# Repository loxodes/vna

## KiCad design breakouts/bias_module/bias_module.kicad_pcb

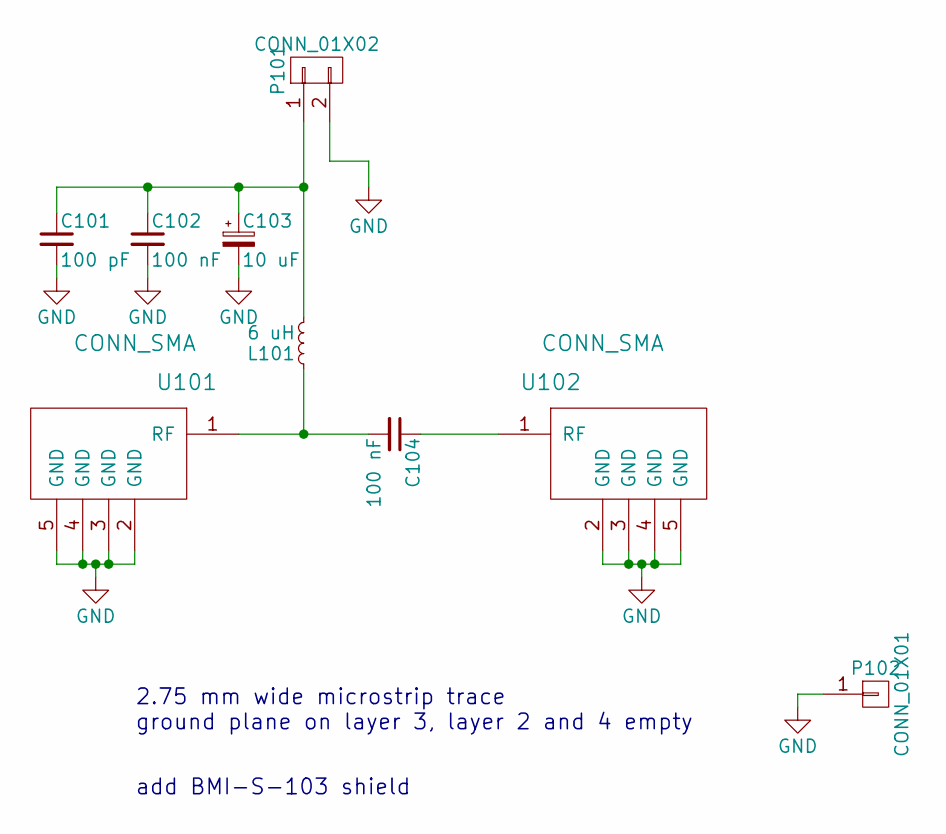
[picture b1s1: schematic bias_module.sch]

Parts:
C101: 100 pF; C_0402
C102: 100 nF; C_0603
C103: 10 uF; C_0805
C104: 100 nF; ATC550L
L101: 6 uH; ATC506WLS
P101: CONN_01X02; TerminalBlock_Pheonix_PT-3.5mm_2pol
P102: CONN_01X01; BMI-S-103-NOSIDES
U101, U102: CONN_SMA; 732511150_sma_thin

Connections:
GND: C101.2, C102.2, C103.2, P101.2, P102.1, U101.2 (GND), U101.3 (GND), U101.4 (GND), U101.5 (GND), U102.2 (GND), U102.3 (GND), U102.4 (GND), U102.5 (GND)
unnamed: C101.1, C102.1, C103.1, L101.2, P101.1
unnamed: C104.1, U102.1 (RF)
unnamed: C104.2, L101.1, U101.1 (RF)

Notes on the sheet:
2.75 mm wide microstrip trace ground plane on layer 3, layer 2 and 4 empty
add BMI-S-103 shield

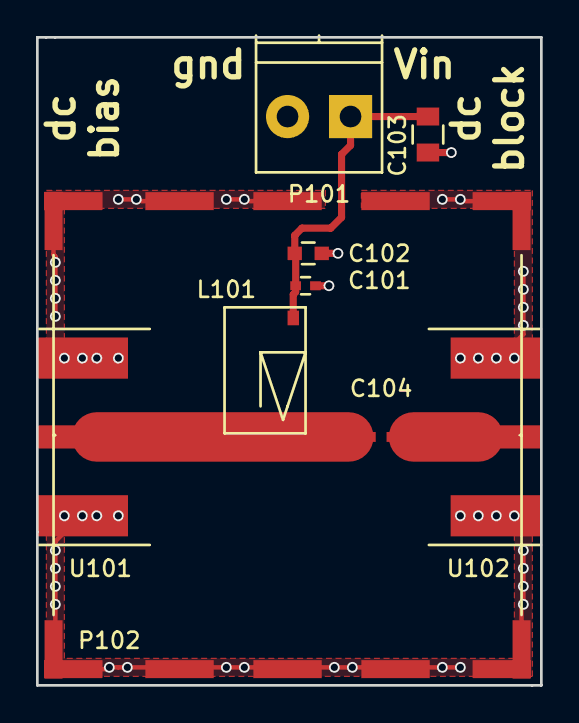
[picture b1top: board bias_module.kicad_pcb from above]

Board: 4 copper layers, 28.0 x 36.0 mm, 9 parts (0 on the bottom side), 4 nets.

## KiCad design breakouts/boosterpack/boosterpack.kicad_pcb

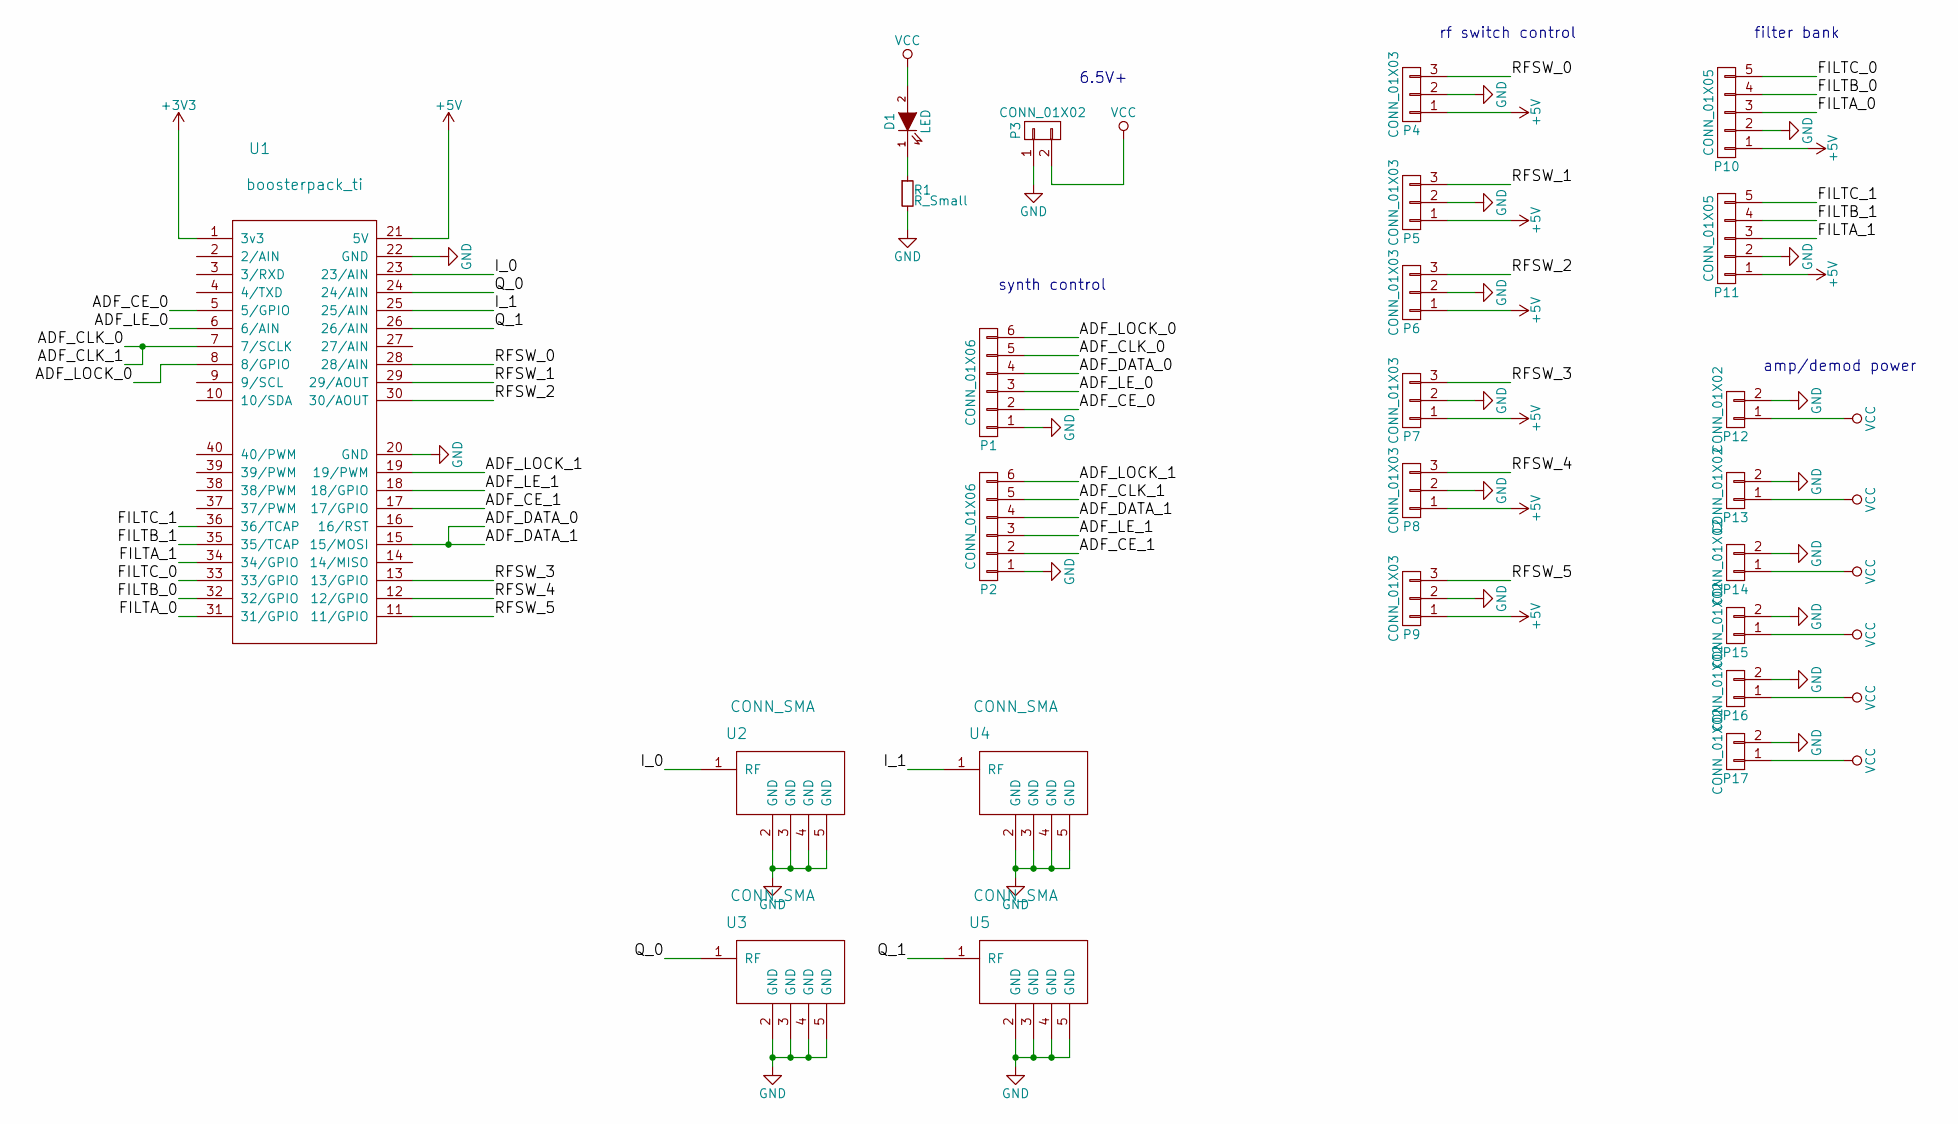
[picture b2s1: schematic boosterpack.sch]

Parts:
D1: LED; LED_0603
P1, P2: CONN_01X06; Pin_Header_Straight_1x06
P3: CONN_01X02; TerminalBlock_Pheonix_PT-3.5mm_2pol
P4, P5, P6, P7, P8, P9: CONN_01X03; Pin_Header_Straight_1x03
P10, P11: CONN_01X05; Pin_Header_Straight_1x05
P12, P13, P14, P15, P16, P17: CONN_01X02; Pin_Header_Straight_1x02
R1: R_Small; R_0603
U1: boosterpack_ti; ti_booster40
U2, U3, U4, U5: CONN_SMA; 732512200_SMA

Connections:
+3V3: U1.1 (3v3)
+5V: P4.1, P5.1, P6.1, P7.1, P8.1, P9.1, P10.1, P11.1, U1.21 (5V)
/ADF_CE_0: P1.2, U1.5 (5/GPIO)
/ADF_CE_1: P2.2, U1.17 (17/GPIO)
/ADF_CLK_0: P1.5, P2.5, U1.7 (7/SCLK)
/ADF_DATA_0: P1.4, P2.4, U1.15 (15/MOSI)
/ADF_LE_0: P1.3, U1.6 (6/AIN)
/ADF_LE_1: P2.3, U1.18 (18/GPIO)
/ADF_LOCK_0: P1.6, U1.8 (8/GPIO)
/ADF_LOCK_1: P2.6, U1.19 (19/PWM)
/FILTA_0: P10.3, U1.31 (31/GPIO)
/FILTA_1: P11.3, U1.34 (34/GPIO)
/FILTB_0: P10.4, U1.32 (32/GPIO)
/FILTB_1: P11.4, U1.35 (35/TCAP)
/FILTC_0: P10.5, U1.33 (33/GPIO)
/FILTC_1: P11.5, U1.36 (36/TCAP)
/I_0: U1.23 (23/AIN), U2.1 (RF)
/I_1: U1.25 (25/AIN), U4.1 (RF)
/Q_0: U1.24 (24/AIN), U3.1 (RF)
/Q_1: U1.26 (26/AIN), U5.1 (RF)
/RFSW_0: P4.3, U1.28 (28/AIN)
/RFSW_1: P5.3, U1.29 (29/AOUT)
/RFSW_2: P6.3, U1.30 (30/AOUT)
/RFSW_3: P7.3, U1.13 (13/GPIO)
/RFSW_4: P8.3, U1.12 (12/GPIO)
/RFSW_5: P9.3, U1.11 (11/GPIO)
GND: P1.1, P2.1, P3.1, P4.2, P5.2, P6.2, P7.2, P8.2, P9.2, P10.2, P11.2, P12.2, P13.2, P14.2, P15.2, P16.2, P17.2, R1.2, U1.20 (GND), U1.22 (GND), U2.2 (GND), U2.3 (GND), U2.4 (GND), U2.5 (GND), U3.2 (GND), U3.3 (GND), U3.4 (GND), U3.5 (GND), U4.2 (GND), U4.3 (GND), U4.4 (GND), U4.5 (GND), U5.2 (GND), U5.3 (GND), U5.4 (GND), U5.5 (GND)
unnamed: D1.1 (K), R1.1
VCC: D1.2 (A), P3.2, P12.1, P13.1, P14.1, P15.1, P16.1, P17.1

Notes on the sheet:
6.5V+
amp/demod power
filter bank
rf switch control
synth control

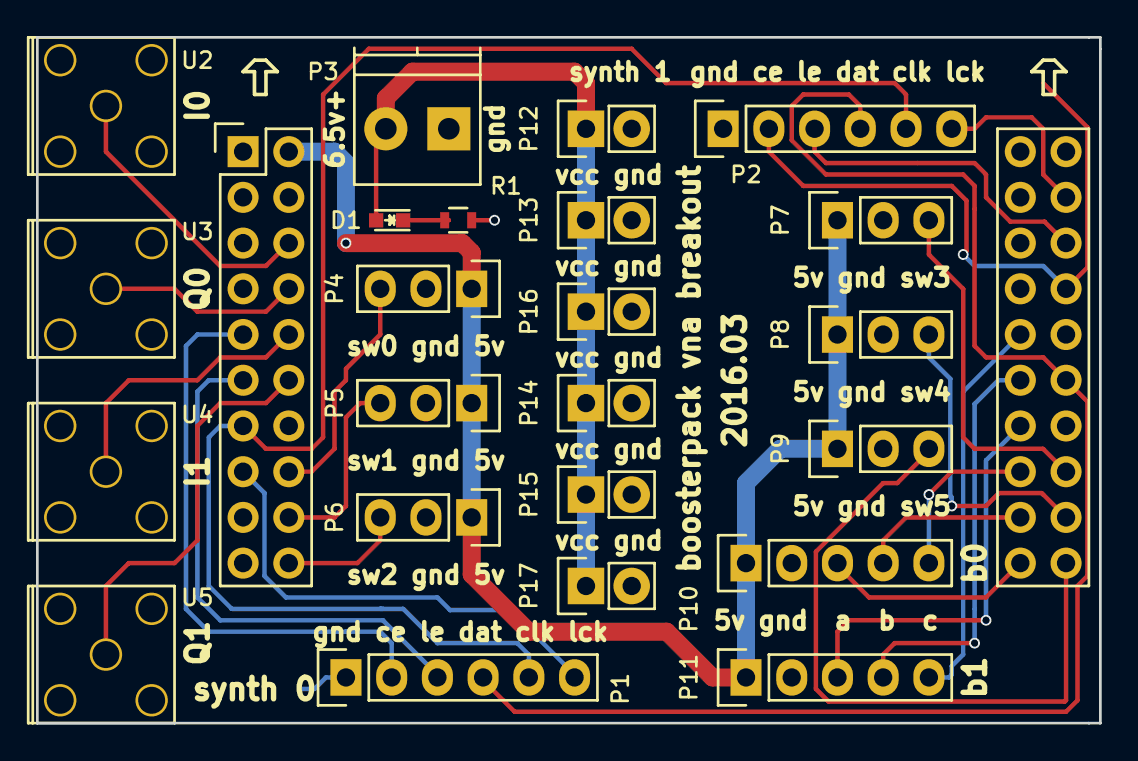
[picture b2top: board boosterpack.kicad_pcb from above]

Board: 2 copper layers, 59.1 x 38.1 mm, 24 parts (0 on the bottom side), 28 nets.

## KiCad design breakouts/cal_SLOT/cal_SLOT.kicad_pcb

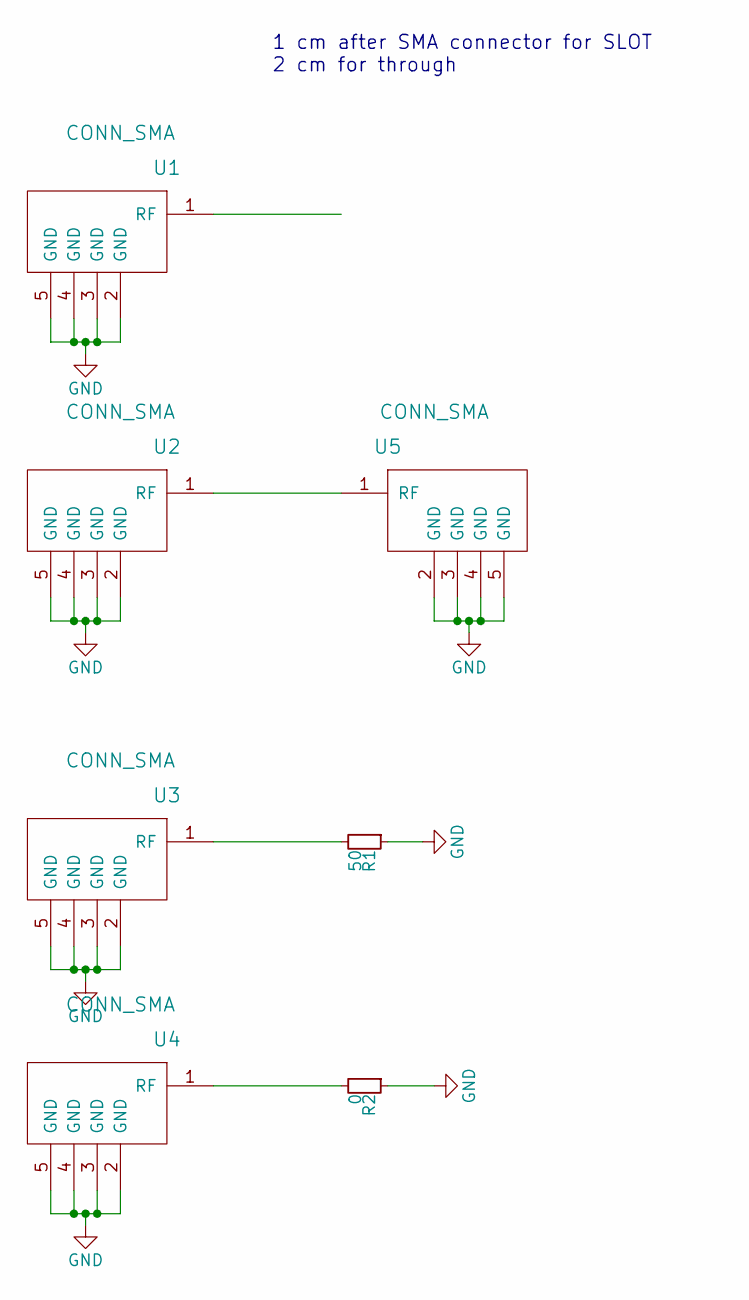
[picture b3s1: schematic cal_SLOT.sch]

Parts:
R1: 50; R_0402
R2: 0; R_0402
U1, U2, U3, U4, U5: CONN_SMA; 732511150_sma_thin

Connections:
GND: R1.1, R2.1, U1.2 (GND), U1.3 (GND), U1.4 (GND), U1.5 (GND), U2.2 (GND), U2.3 (GND), U2.4 (GND), U2.5 (GND), U3.2 (GND), U3.3 (GND), U3.4 (GND), U3.5 (GND), U4.2 (GND), U4.3 (GND), U4.4 (GND), U4.5 (GND), U5.2 (GND), U5.3 (GND), U5.4 (GND), U5.5 (GND)
unnamed: R1.2, U3.1 (RF)
unnamed: R2.2, U4.1 (RF)
unnamed: U2.1 (RF), U5.1 (RF)

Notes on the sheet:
1 cm after SMA connector for SLOT 2 cm for through

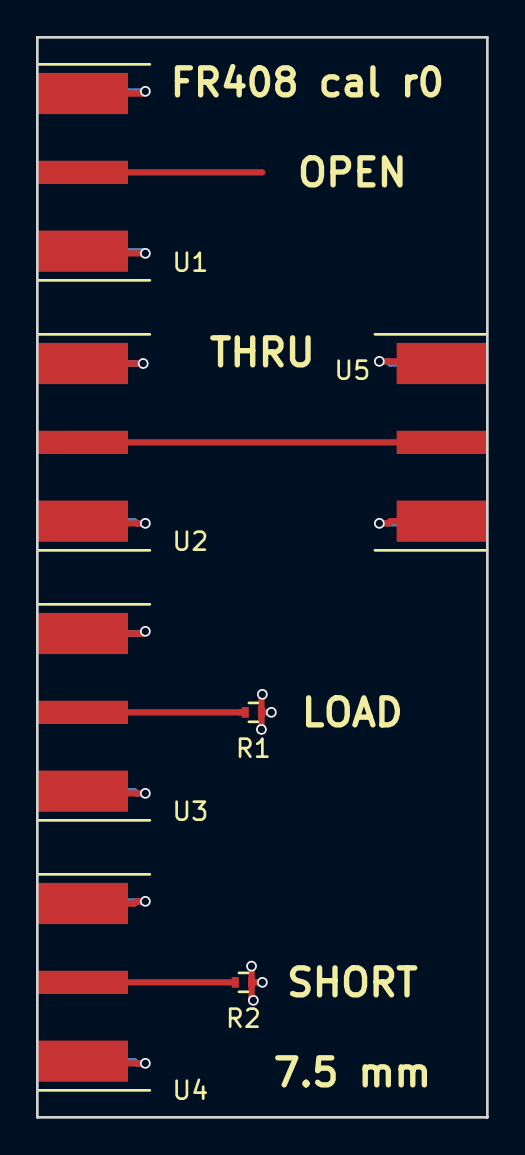
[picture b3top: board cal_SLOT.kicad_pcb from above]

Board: 4 copper layers, 25.0 x 60.0 mm, 7 parts (0 on the bottom side), 4 nets.

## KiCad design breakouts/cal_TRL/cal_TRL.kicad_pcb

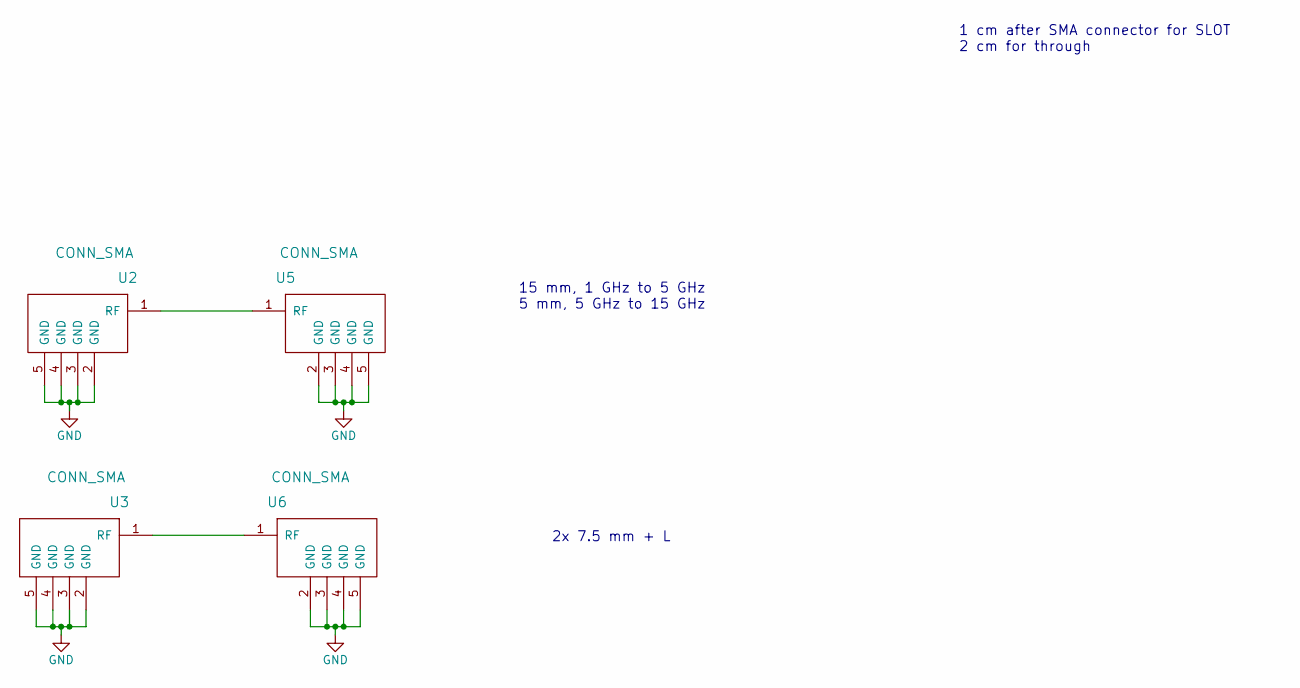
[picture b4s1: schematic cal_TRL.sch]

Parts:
U2, U3, U5, U6: CONN_SMA; 732511150_sma_thin

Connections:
GND: U2.2 (GND), U2.3 (GND), U2.4 (GND), U2.5 (GND), U3.2 (GND), U3.3 (GND), U3.4 (GND), U3.5 (GND), U5.2 (GND), U5.3 (GND), U5.4 (GND), U5.5 (GND), U6.2 (GND), U6.3 (GND), U6.4 (GND), U6.5 (GND)
unnamed: U2.1 (RF), U5.1 (RF)
unnamed: U3.1 (RF), U6.1 (RF)

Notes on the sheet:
1 cm after SMA connector for SLOT 2 cm for through
2x 7.5 mm + L
15 mm, 1 GHz to 5 GHz 5 mm, 5 GHz to 15 GHz

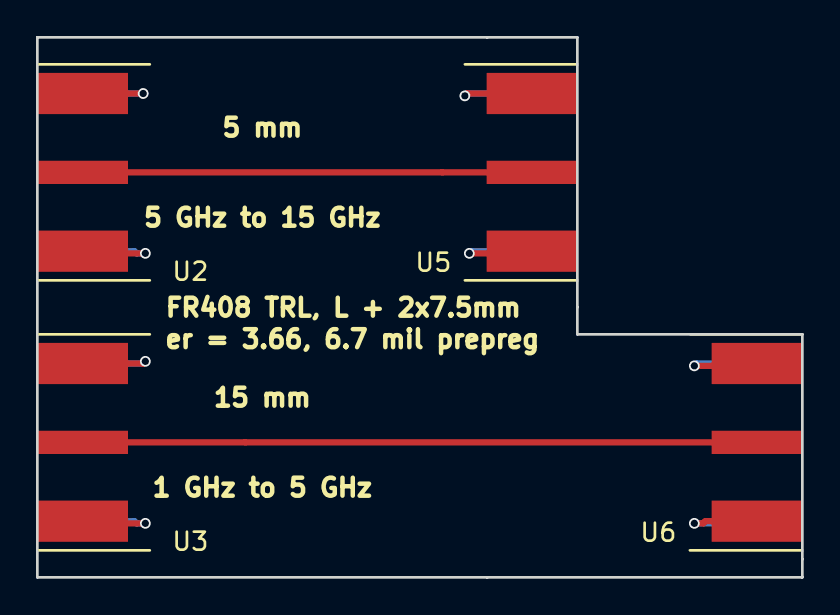
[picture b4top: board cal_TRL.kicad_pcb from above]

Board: 4 copper layers, 42.5 x 30.0 mm, 4 parts (0 on the bottom side), 3 nets.

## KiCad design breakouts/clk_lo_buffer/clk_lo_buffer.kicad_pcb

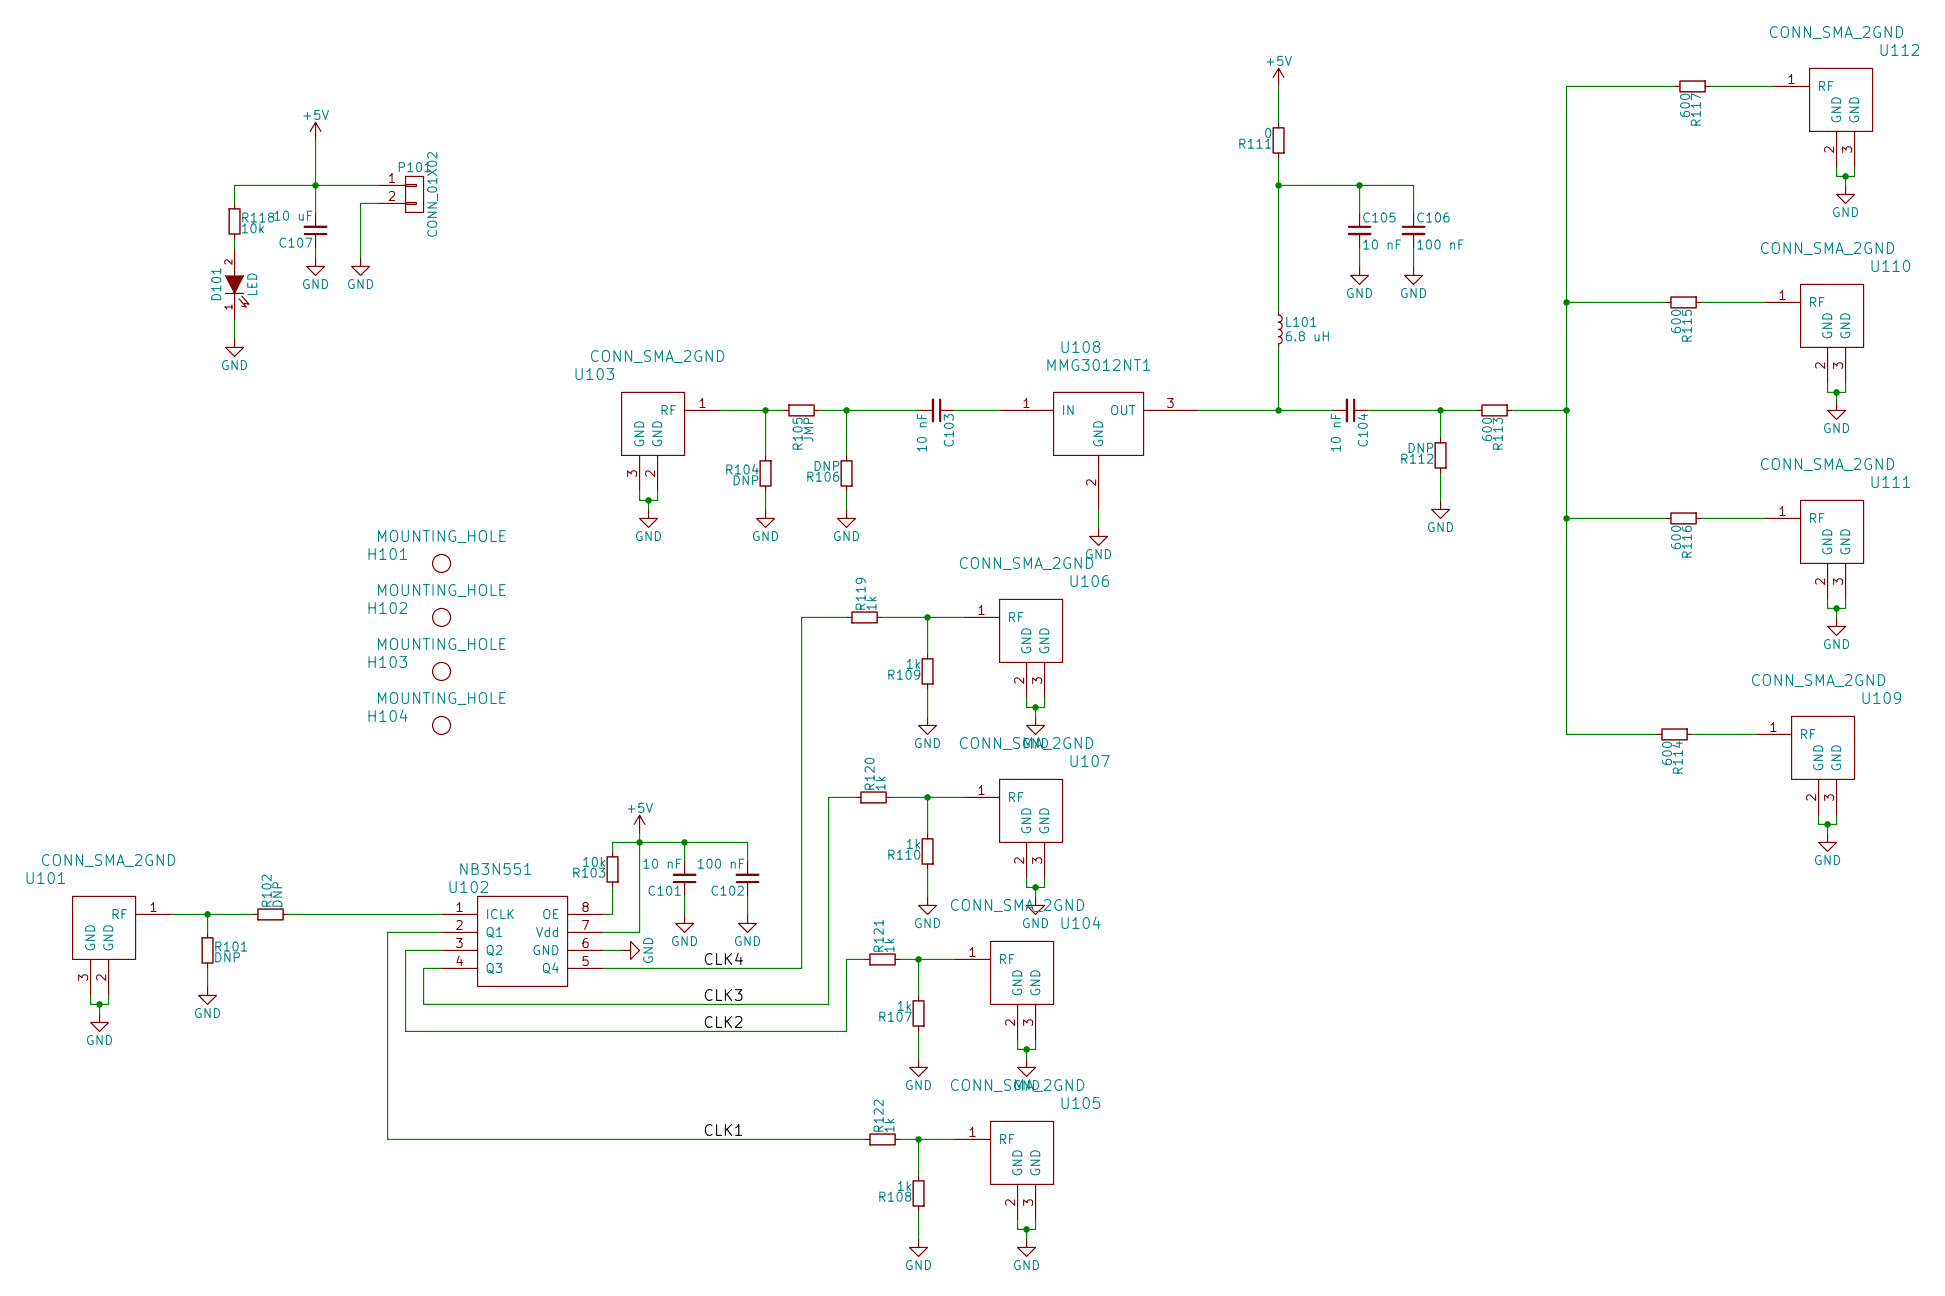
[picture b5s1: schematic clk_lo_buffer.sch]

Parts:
C101, C103, C104, C105: 10 nF; C_0603
C102, C106: 100 nF; C_0603
C107: 10 uF; C_0603
D101: LED; LED_0603
H101, H102, H103, H104: MOUNTING_HOLE; MountingHole_2-7mm
L101: 6.8 uH; R_0603
P101: CONN_01X02; TerminalBlock_Pheonix_PT-3.5mm_2pol
R101, R102, R104, R106, R112: DNP; R_0603
R103, R118: 10k; R_0603
R105: JMP; R_0603
R107, R108, R109, R110, R119, R120, R121, R122: 1k; R_0603
R111: 0; R_0603
R113, R114, R115, R116, R117: 600; R_0603
U101, U103, U104, U105, U106, U107, U109, U110, U111, U112: CONN_SMA_2GND; 734120110_ufl_umc
U102: NB3N551; SOIC-8_3.9x4.9mm_Pitch1.27mm
U108: MMG3012NT1; SOT89-3_Housing

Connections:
+5V: C101.2, C102.2, C107.2, P101.1, R103.2, R111.2, R118.1, U102.7 (Vdd)
/CLK1: R122.1, U102.2 (Q1)
/CLK2: R121.1, U102.3 (Q2)
/CLK3: R120.1, U102.4 (Q3)
/CLK4: R119.1, U102.5 (Q4)
GND: C101.1, C102.1, C105.2, C106.2, C107.1, D101.1 (K), P101.2, R101.2, R104.2, R106.1, R107.1, R108.1, R109.1, R110.1, R112.1, U101.2 (GND), U101.3 (GND), U102.6 (GND), U103.2 (GND), U103.3 (GND), U104.2 (GND), U104.3 (GND), U105.2 (GND), U105.3 (GND), U106.2 (GND), U106.3 (GND), U107.2 (GND), U107.3 (GND), U108.2 (GND), U109.2 (GND), U109.3 (GND), U110.2 (GND), U110.3 (GND), U111.2 (GND), U111.3 (GND), U112.2 (GND), U112.3 (GND)
unnamed: C103.1, U108.1 (IN)
unnamed: C103.2, R105.2, R106.2
unnamed: C104.1, R112.2, R113.2
unnamed: C104.2, L101.2, U108.3 (OUT)
unnamed: C105.1, C106.1, L101.1, R111.1
unnamed: D101.2 (A), R118.2
unnamed: R101.1, R102.1, U101.1 (RF)
unnamed: R102.2, U102.1 (ICLK)
unnamed: R103.1, U102.8 (OE)
unnamed: R104.1, R105.1, U103.1 (RF)
unnamed: R107.2, R121.2, U104.1 (RF)
unnamed: R108.2, R122.2, U105.1 (RF)
unnamed: R109.2, R119.2, U106.1 (RF)
unnamed: R110.2, R120.2, U107.1 (RF)
unnamed: R113.1, R114.2, R115.2, R116.2, R117.2
unnamed: R114.1, U109.1 (RF)
unnamed: R115.1, U110.1 (RF)
unnamed: R116.1, U111.1 (RF)
unnamed: R117.1, U112.1 (RF)

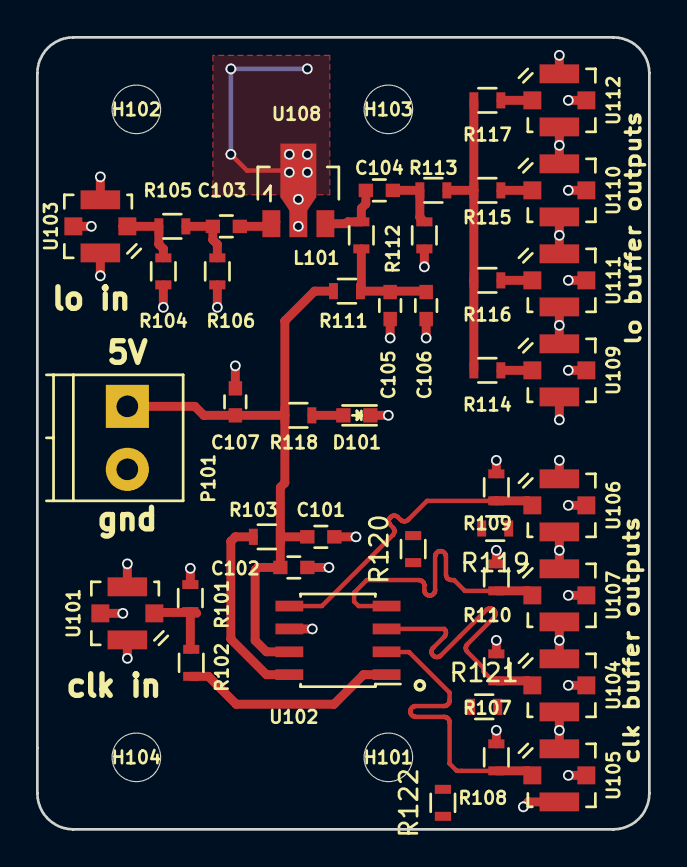
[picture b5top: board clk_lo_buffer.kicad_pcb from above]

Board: 2 copper layers, 34.0 x 44.0 mm, 48 parts (0 on the bottom side), 25 nets.

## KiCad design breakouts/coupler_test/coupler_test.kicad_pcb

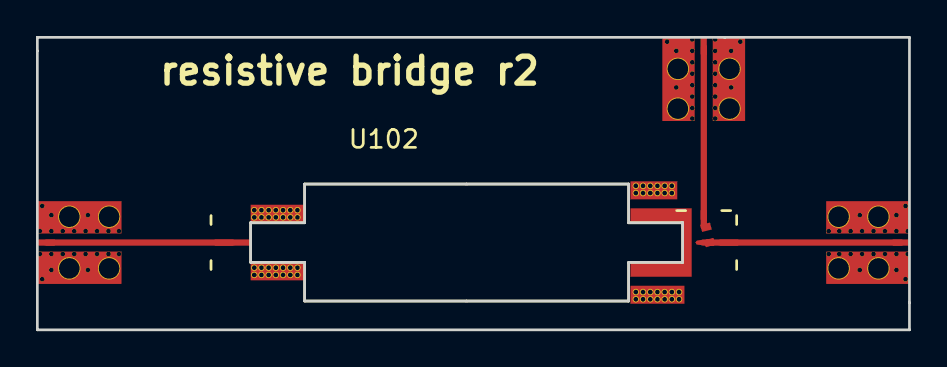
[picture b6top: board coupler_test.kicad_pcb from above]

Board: 4 copper layers, 48.5 x 16.2 mm, 4 parts (0 on the bottom side), 4 nets.

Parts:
U101, U103, U104: CONN_SMA_2GND; SMA_901-10512_6p7MIL_FR408_CPW_LAUNCH
U102: resistive_bridge; resistive_bridge_osh_fr408_ustrip

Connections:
GND: U101.2, U101.3, U102.4, U103.2, U103.3, U104.2, U104.3
unnamed: U101.1, U102.1
unnamed: U102.2, U104.1
unnamed: U102.3, U103.1

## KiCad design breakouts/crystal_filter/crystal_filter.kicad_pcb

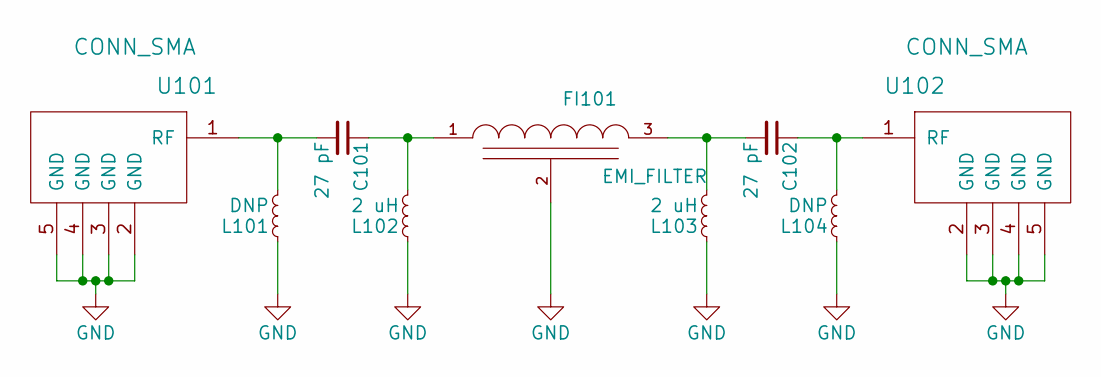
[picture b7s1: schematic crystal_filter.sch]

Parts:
C101, C102: 27 pF; C_0805
FI101: EMI_FILTER; ECS-96SMF
L101, L104: DNP; C_0805
L102, L103: 2 uH; C_0805
U101, U102: CONN_SMA; 732512200_SMA

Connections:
GND: FI101.2 (GND), L101.1, L102.1, L103.1, L104.1, U101.2 (GND), U101.3 (GND), U101.4 (GND), U101.5 (GND), U102.2 (GND), U102.3 (GND), U102.4 (GND), U102.5 (GND)
unnamed: C101.1, FI101.1 (VI), L102.2
unnamed: C101.2, L101.2, U101.1 (RF)
unnamed: C102.1, L104.2, U102.1 (RF)
unnamed: C102.2, FI101.3 (VO), L103.2

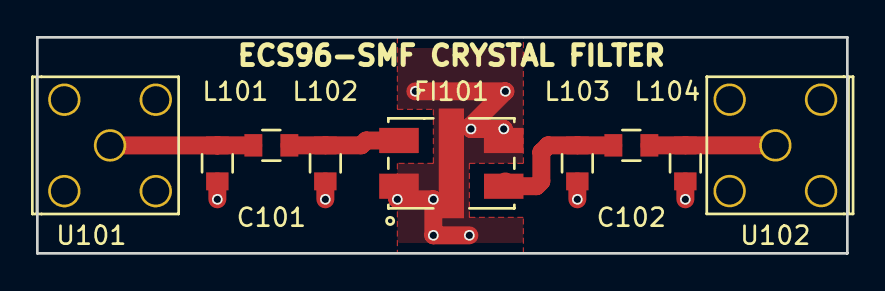
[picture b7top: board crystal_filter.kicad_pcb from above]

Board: 2 copper layers, 45.0 x 12.0 mm, 9 parts (0 on the bottom side), 5 nets.
